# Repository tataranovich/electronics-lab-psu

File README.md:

# Lab PSU

Linear power supply with 5 fixed outputs (+12V, +5V, +3.3V, -5V, -12V).

**Features:**

- 5 linear outputs: +12V, +5V, +3.3V, -5V, -12V
- Up to 1A of current for positive and negative rail
- Current indication on both rails
- Low noise (25mV peak-peak on negative rail, 15mV peak-peak on positive rail)
- Temperature controlled fan

**Assembly notes**

- Power supply case: Kradex Z17
- AC transformer: 40W toroid with 18V secondary
- Ammeters: 91C16 with [custom scale](./scale/91C16%20scale.svg) created using [Scale Master](https://soulmare.github.io/scale_master/)
- Cooling: CMDK8-7I52D-A5-GP or equivalent (70mm fan)
- [Schematic and PCB](./kicad) created using KiCad
- [Case panels](./panels) created using LibreCad and FreeCad

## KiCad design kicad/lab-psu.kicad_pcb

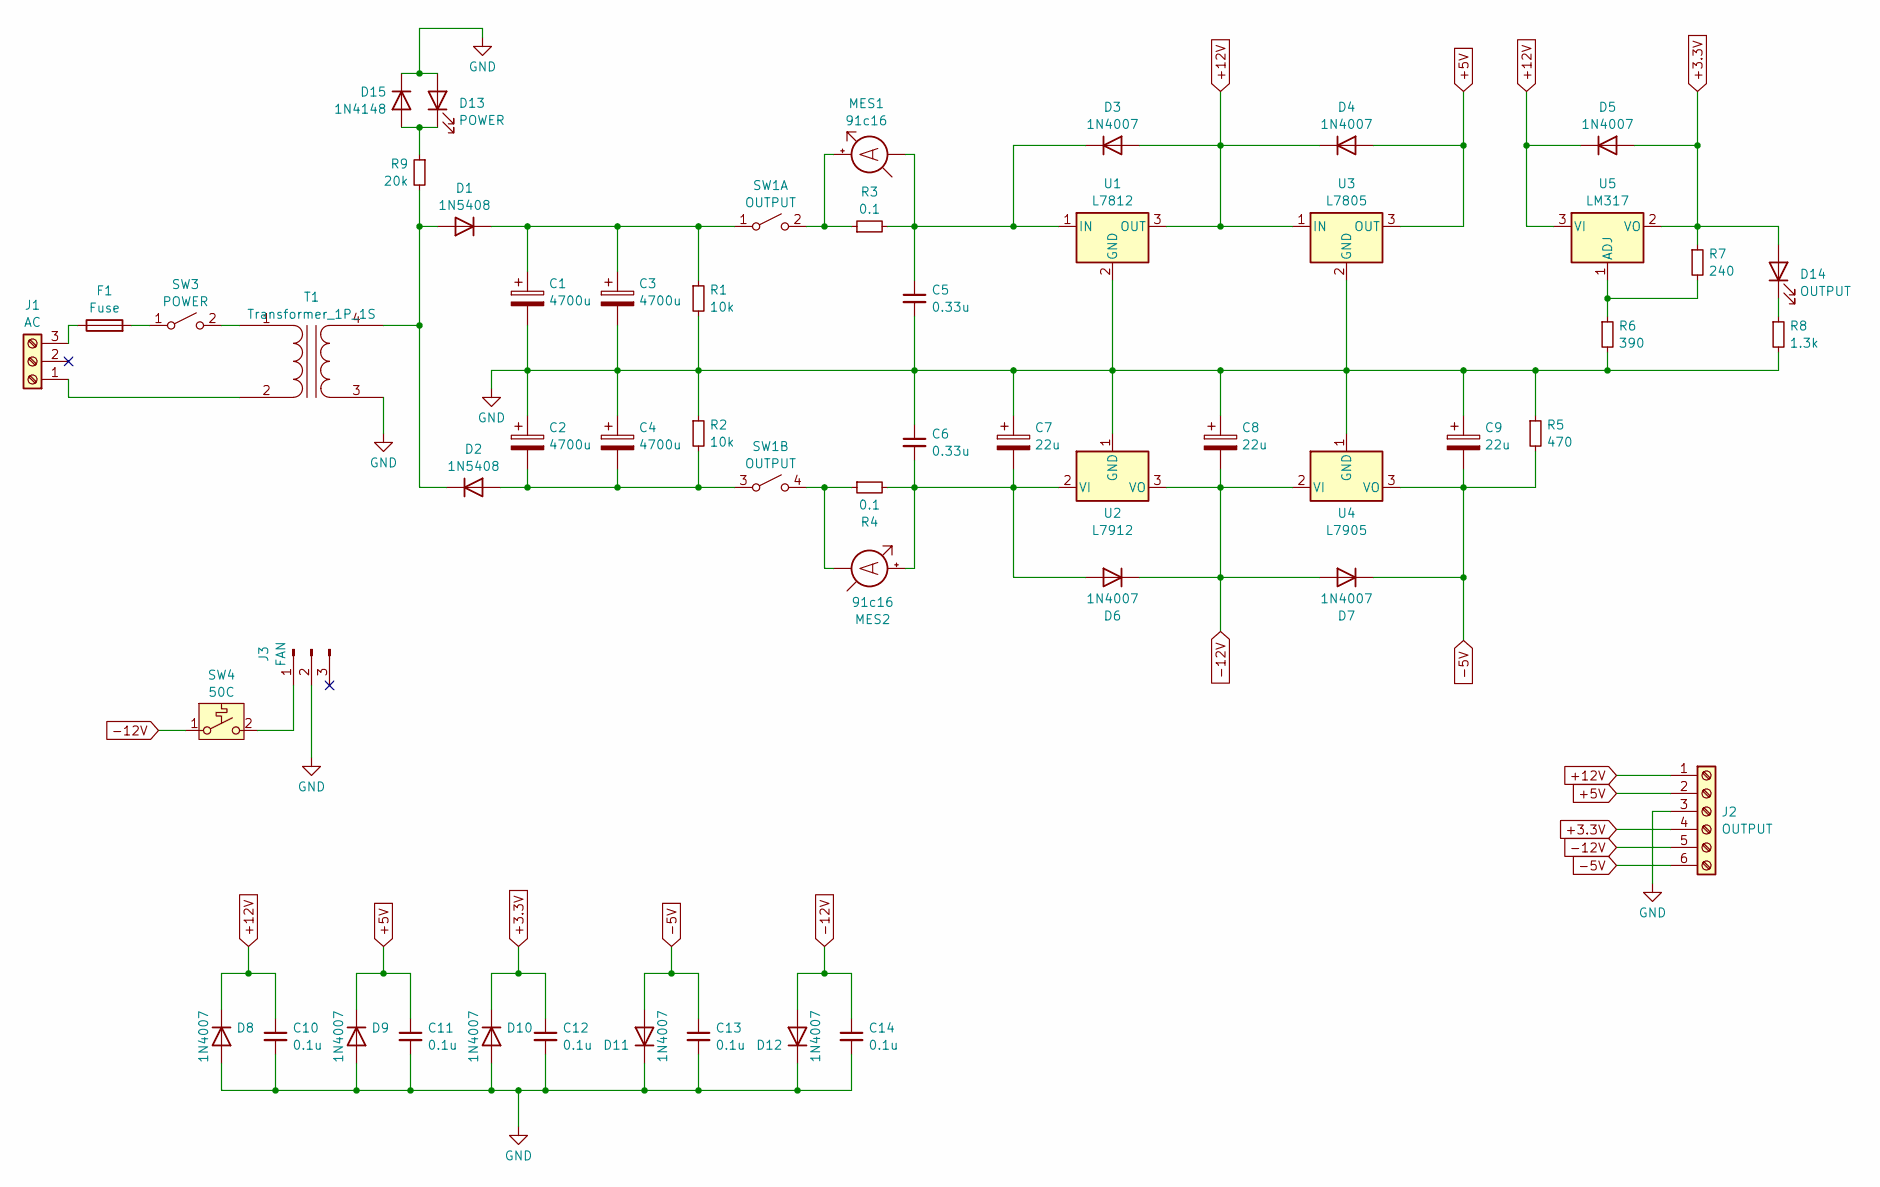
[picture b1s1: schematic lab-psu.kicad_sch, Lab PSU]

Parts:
C1, C2, C3, C4: 4700u; CP_Radial_D22.0mm_P10.00mm_SnapIn
C5, C6: 0.33u; C_Disc_D4.7mm_W2.5mm_P5.00mm
C7, C8, C9: 22u; CP_Radial_D5.0mm_P2.50mm
C10, C11, C12, C13, C14: 0.1u; C_Disc_D4.7mm_W2.5mm_P5.00mm
D1, D2: 1N5408; D_DO-201AD_P15.24mm_Horizontal
D3, D4, D5, D6, D7, D8, D9, D10, D11, D12: 1N4007; D_DO-41_SOD81_P10.16mm_Horizontal
D13: POWER; LED_D5.0mm
D14: OUTPUT; LED_D5.0mm
D15: 1N4148; D_DO-35_SOD27_P7.62mm_Horizontal
F1: Fuse; Fuseholder_Cylinder-5x20mm_Schurter_0031_8201_Horizontal_Op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
J1: AC; TerminalBlock_Altech_AK300-3_P5.00mm
J2: OUTPUT; TerminalBlock_bornier-6_P5.08mm
J3: FAN; PinHeader_1x03_P2.54mm_Vertical
MES1, MES2: 91c16; PinHeader_1x02_P2.54mm_Vertical
R1, R2: 10k; R_Axial_DIN0207_L6.3mm_D2.5mm_P10.16mm_Horizontal
R3, R4: 0.1; R_Axial_Power_L25.0mm_W6.4mm_P30.48mm
R5: 470; R_Axial_DIN0207_L6.3mm_D2.5mm_P10.16mm_Horizontal
R6: 390; R_Axial_DIN0207_L6.3mm_D2.5mm_P10.16mm_Horizontal
R7: 240; R_Axial_DIN0207_L6.3mm_D2.5mm_P10.16mm_Horizontal
R8: 1.3k; R_Axial_DIN0207_L6.3mm_D2.5mm_P10.16mm_Horizontal
R9: 20k; R_Axial_DIN0207_L6.3mm_D2.5mm_P10.16mm_Horizontal
SW1: OUTPUT; SW_Push_2P1T_Toggle_CK_PVA1xxH4xxxxxxV2
SW3: POWER; TerminalBlock_bornier-2_P5.08mm
SW4: 50C; PinHeader_1x02_P2.54mm_Vertical
T1: Transformer_1P_1S; Transformer_Toroid_Tapped_Horizontal_D70.0mm
U1: L7812; TO-220-3_Vertical
U2: L7912; TO-220-3_Vertical
U3: L7805; TO-220-3_Vertical
U4: L7905; TO-220-3_Vertical
U5: LM317; TO-220-3_Vertical

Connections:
+3.3V: C12.1, D5.2 (A), D10.1 (K), D14.2 (A), J2.4, R7.1, U5.2 (VO)
+5V: C11.1, D4.2 (A), D9.1 (K), J2.2, U3.3 (OUT)
+12V: C10.1, D3.2 (A), D4.1 (K), D5.1 (K), D8.1 (K), J2.1, U1.3 (OUT), U3.1 (IN), U5.3 (VI)
-5V: C9.2, C13.1, D7.1 (K), D11.2 (A), J2.6, R5.2, U4.3 (VO)
-12V: C8.2, C14.1, D6.1 (K), D7.2 (A), D12.2 (A), J2.5, SW4.1 (A), U2.3 (VO), U4.2 (VI)
GND: C1.2, C2.1, C3.2, C4.1, C5.2, C6.1, C7.1, C8.1, C9.1, C10.2, C11.2, C12.2, C13.2, C14.2, D8.2 (A), D9.2 (A), D10.2 (A), D11.1 (K), D12.1 (K), D13.2 (A), D15.1 (K), J2.3, J3.2, R1.2, R2.1, R5.1, R6.2, R8.2, T1.3 (SA), U1.2 (GND), U2.1 (GND), U3.2 (GND), U4.1 (GND)
unnamed: D1.2 (A), D2.1 (K), R9.2, T1.4 (SB)
unnamed: C1.1, C3.1, D1.1 (K), R1.1, SW1.1 (A)
unnamed: C2.2, C4.2, D2.2 (A), R2.2, SW1.3 (A)
unnamed: C5.1, D3.1 (K), MES1.1 (-), R3.2, U1.1 (IN)
unnamed: C6.2, C7.2, D6.2 (A), MES2.2 (+), R4.2, U2.2 (VI)
unnamed: D13.1 (K), D15.2 (A), R9.1
unnamed: D14.1 (K), R8.1
unnamed: J1.1, T1.2 (AB)
unnamed: F1.1, J1.3
unnamed: J3.1, SW4.2 (B)
unnamed: MES1.2 (+), R3.1, SW1.2 (B)
unnamed: MES2.1 (-), R4.1, SW1.4 (B)
unnamed: F1.2, SW3.1 (A)
unnamed: SW3.2 (B), T1.1 (AA)
unnamed: R6.1, R7.2, U5.1 (ADJ)

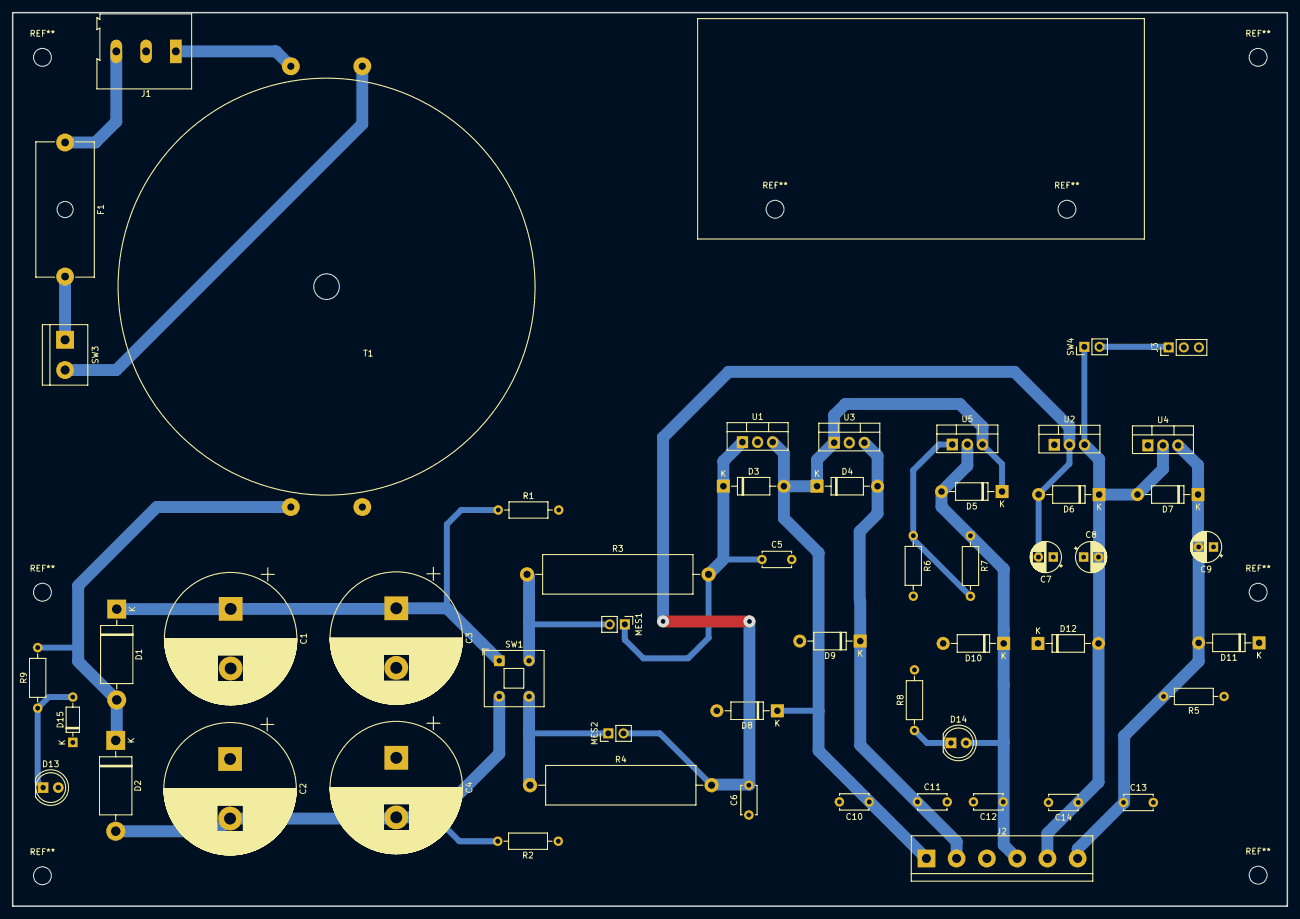
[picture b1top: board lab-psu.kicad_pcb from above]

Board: 2 copper layers, 214.0 x 150.0 mm, 53 parts (0 on the bottom side), 21 nets.

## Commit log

2024-03-19 Lab PSU revision 2
2024-12-14 Refactor front panel, add STL files for 3D printing
